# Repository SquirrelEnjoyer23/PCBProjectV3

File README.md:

# PCBProjectV3
Version 3 of the PCB
This PCB is a owl shaped pcb that has two lights for eyes!

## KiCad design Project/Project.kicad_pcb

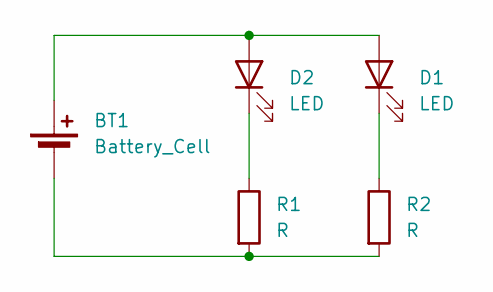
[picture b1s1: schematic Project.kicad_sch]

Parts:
BT1: Battery_Cell; BatteryHolder_Keystone_3034_1x20mm
D1, D2: LED; LED_D5.0mm
R1, R2: R; R_Axial_DIN0207_L6.3mm_D2.5mm_P7.62mm_Horizontal

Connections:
unnamed: BT1.1 (+), D1.2 (A), D2.2 (A)
unnamed: BT1.2 (-), R1.2, R2.2
unnamed: D1.1 (K), R2.1
unnamed: D2.1 (K), R1.1

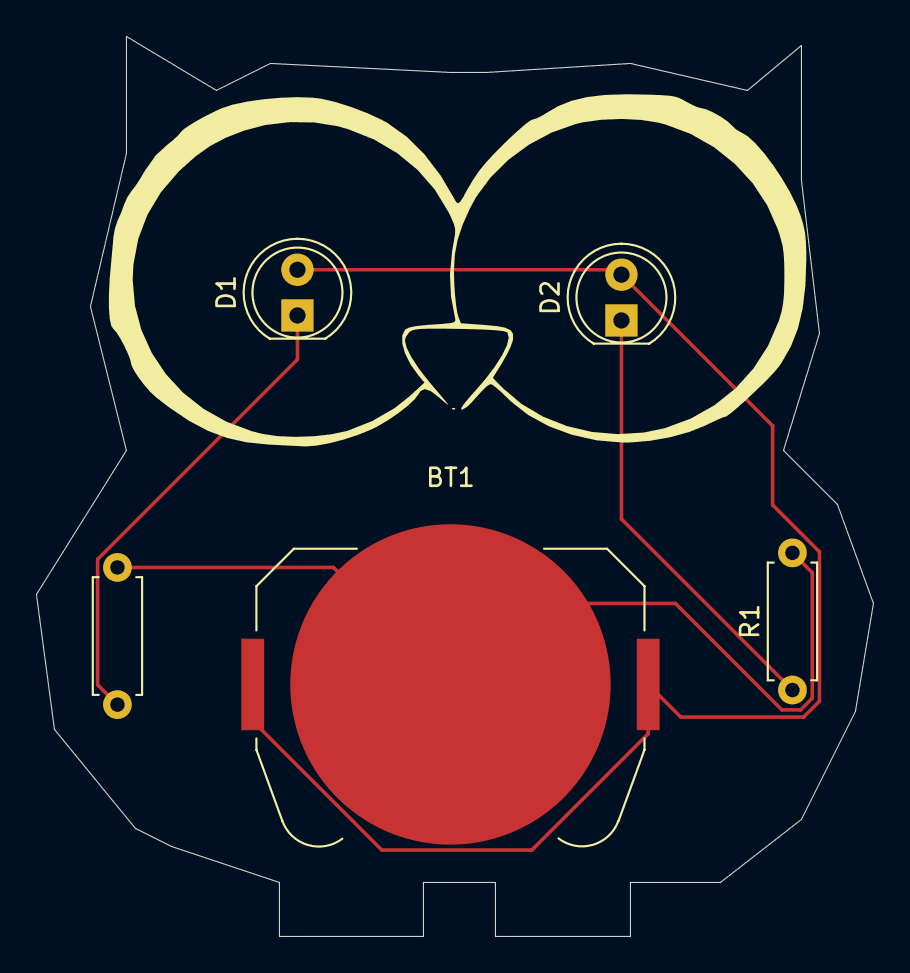
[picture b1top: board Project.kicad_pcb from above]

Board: 2 copper layers, 46.5 x 50.0 mm, 5 parts (0 on the bottom side), 4 nets.
